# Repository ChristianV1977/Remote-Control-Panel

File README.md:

# Remote-Control-Panel
Remote-Control-Panel for Hackster Arduino Maker Challenge

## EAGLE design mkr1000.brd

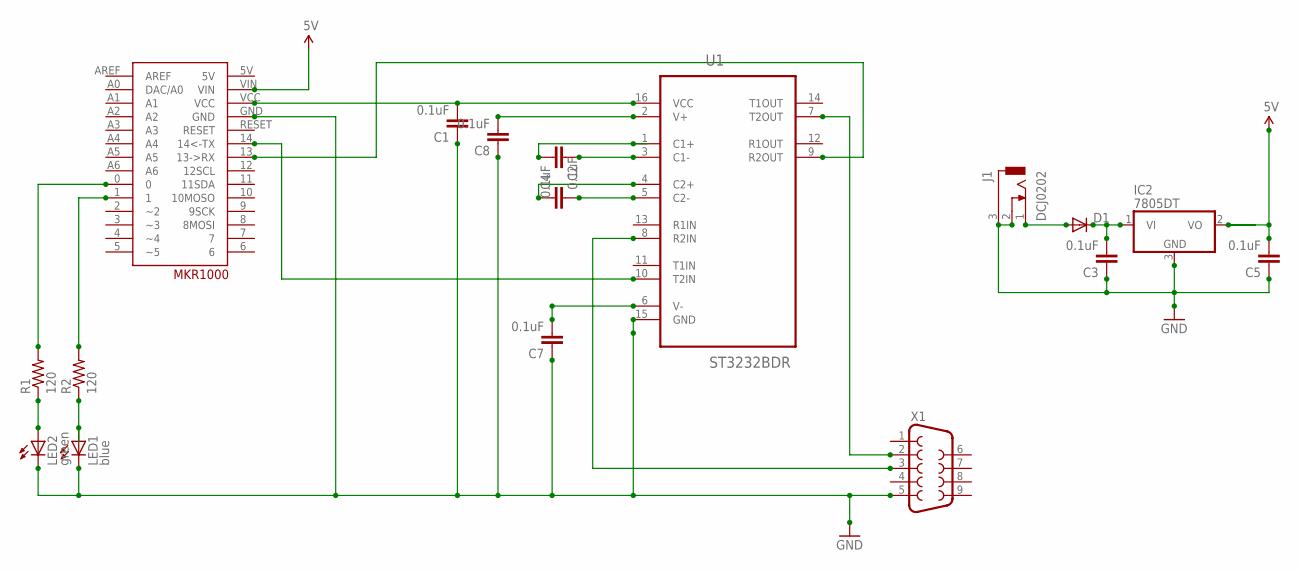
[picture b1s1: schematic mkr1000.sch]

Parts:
C1, C2, C3, C4, C5, C7, C8: 0.1uF; 0603-CAP
D1: DIODE-SMB; SMB
IC2: 7805DT; TO252
J1: DCJ0202
LED1: blue; SML0805
LED2: green; SML0805
MKR1000: MKR1000
R1, R2: 120; 0805
U1: ST3232BDR; SOIC127P600X175-16N
X1: DB9FEMALE; DB9

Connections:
3.3V: C1.2, MKR1000.VCC, U1.16 (VCC)
5V: C5.2, IC2.2 (VO), MKR1000.VIN
GND: C1.1, C3.1, C5.1, C7.1, C8.1, IC2.3 (GND), J1.2, J1.3 (1), LED1.C, LED2.C, MKR1000.GND, U1.15 (GND), X1.5
unnamed: D1.A, J1.1 (3)
unnamed: C3.2, D1.C, IC2.1 (VI)
unnamed: LED2.A, R1.1
unnamed: U1.7 (T2OUT), X1.2
unnamed: C7.2, U1.6 (V-)
unnamed: C8.2, U1.2 (V+)
unnamed: C2.2, U1.1 (C1+)
unnamed: C2.1, U1.3 (C1-)
unnamed: C4.1, U1.4 (C2+)
unnamed: C4.2, U1.5 (C2-)
unnamed: MKR1000.14 (14<-TX), U1.10 (T2IN)
unnamed: LED1.A, R2.1
unnamed: MKR1000.0, R1.2
unnamed: MKR1000.1, R2.2
unnamed: U1.8 (R2IN), X1.3
unnamed: MKR1000.13 (13->RX), U1.9 (R2OUT)

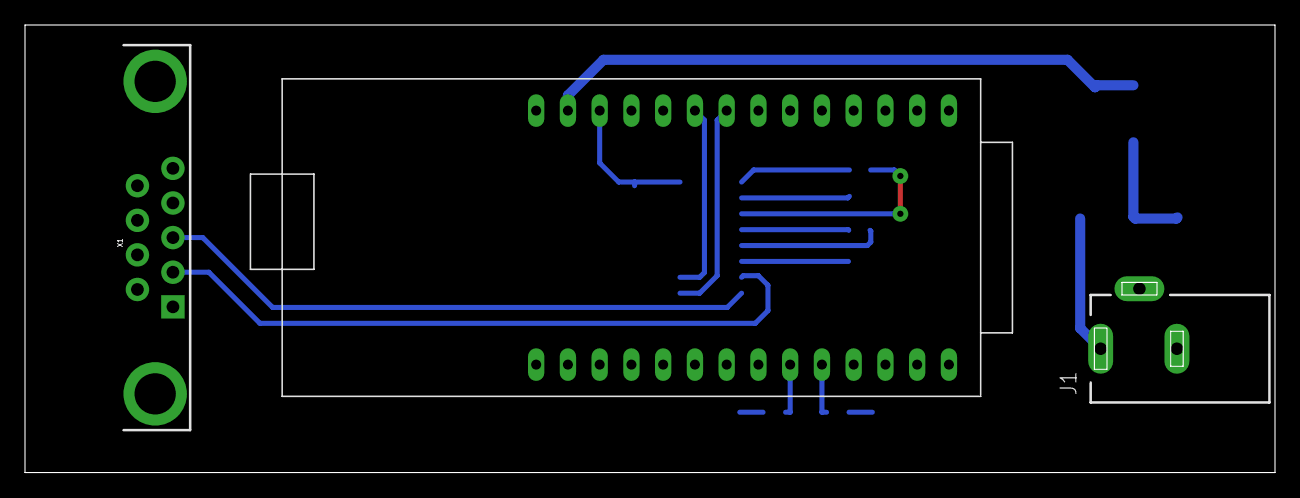
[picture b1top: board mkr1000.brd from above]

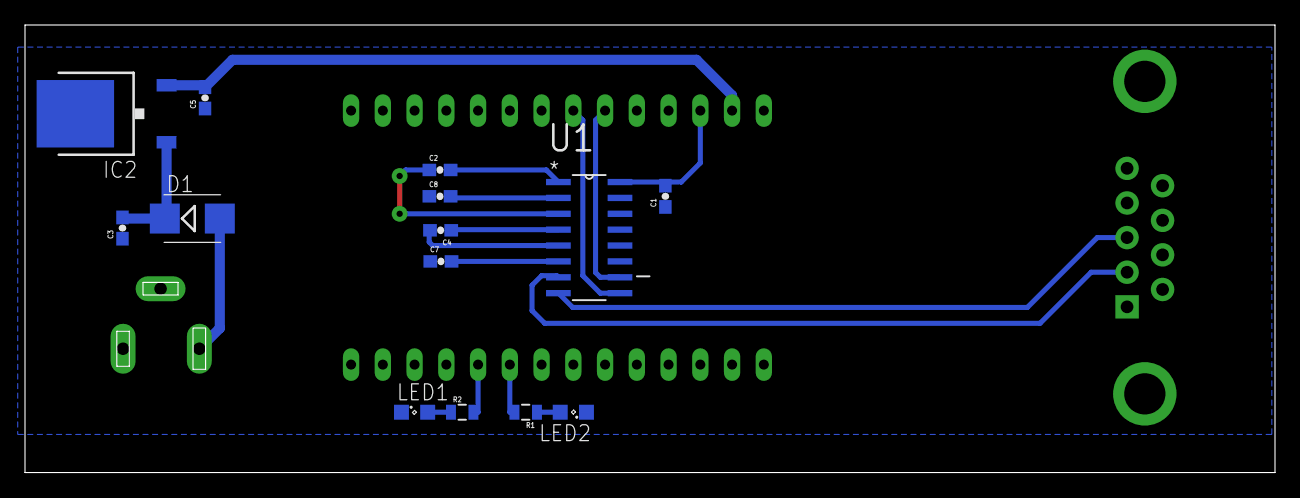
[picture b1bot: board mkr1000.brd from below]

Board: 2 copper layers, 100.0 x 35.8 mm, 17 parts (14 on the bottom side), 19 nets.

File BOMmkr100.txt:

Part Value     Device                    Package             Description                  
C1   0.1uF     0.1UF-25V(+80/-20%)(0603) 0603-CAP            CAP-00810                    
C2   0.1uF     0.1UF-25V(+80/-20%)(0603) 0603-CAP            CAP-00810                    
C3   0.1uF     0.1UF-25V(+80/-20%)(0603) 0603-CAP            CAP-00810                    
C4   0.1uF     0.1UF-25V(+80/-20%)(0603) 0603-CAP            CAP-00810                    
C5   0.1uF     0.1UF-25V(+80/-20%)(0603) 0603-CAP            CAP-00810                    
C7   0.1uF     0.1UF-25V(+80/-20%)(0603) 0603-CAP            CAP-00810                    
C8   0.1uF     0.1UF-25V(+80/-20%)(0603) 0603-CAP            CAP-00810                    
D1             DIODE-SMB                 SMB                 DIODE                        
IC2  7805DT    7805DT                    TO252               Positive VOLTAGE REGULATOR   
J1   DCJ0202   DCJ0202                   DCJ0202             DC POWER JACK                
LED1 blue      LEDSML0805                SML0805             LED                          
LED2 green     LEDSML0805                SML0805             LED                          
R1   120       RESISTOR0805-RES          0805                Resistor                     
R2   120       RESISTOR0805-RES          0805                Resistor                     
U$1  MKR1000   MKR1000                   MKR1000                                          
U1   ST3232BDR ST3232BDR                 SOIC127P600X175-16N RS-232 drivers and receivers 
X1             DB9FEMALE                 DB9                 DB9 Connector      
T1   6V DC     Adaptor

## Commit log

2016-03-24 Added files via upload
    EagleCad layout files for the MKR1000 to serial adaptor board
2016-03-24 Arduino sketch for remote control panel.
    Arduino sketch for remote control panel.
2016-03-25 Cleanup
    Cleanup
2016-03-26 Clean
2016-03-26 BOM
    Clean
2016-03-26 Clean
    Clean
2016-03-28 Clean
    PDF of TTL to RS232

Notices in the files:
parts and their libraries:
SparkFun-Capacitors: Licensing: CC v3.0 Share-Alike You are welcome to use this library for commercial purposes.
